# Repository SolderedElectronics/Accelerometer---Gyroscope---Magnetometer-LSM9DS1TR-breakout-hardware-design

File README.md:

# Accelerometer & Gyroscope & Magnetometer LSM9DS1TR 9-DOF breakout Hardware Design

## About the Product

|  |
| :----------------------------------------------------------: |
| [Buy Accelerometer & Gyroscope & Magnetometer LSM9DS1TR 9-DOF breakout](https://www.solde.red/333069) |

Discover the magic of motion tracking with our all-in-one Accelerometer, Gyroscope & Magnetometer LSM9DS1TR Breakout! This mini but mighty module bundles together a 3D accelerometer, a 3D gyroscope, and a 3D magnetometer. It lets you monitor not only linear and rotational movements but also the magnetic field surrounding your projects. Despite its pocket-size, it offers high-accuracy measurements — ±16 g for the accelerometer, ±2000 dps for the gyroscope, and ±16 Gauss for the magnetometer.

It has an embedded temperature sensor, FIFO buffer for data management, and interrupt features to signal your microcontroller when data is ready or when a certain event occurs. Plus, with I2C interface, it can easily connect with a variety of microcontrollers.

Our LSM9DS1TR breakout merges high-end capabilities with a user-friendly approach. It operates within a supply voltage range of 2.4V to 3.6V, making it compatible with both 3.3V and 5V systems. Its low-power and power-down modes optimize performance without draining too much energy.

This breakout board comes with 2 easyC connectors which will simplify connection with microcontrollers. By using the easyC module connection system, forget about incorrectly connected or, in the worst case, damaged modules.

---

## Repository Contents

This repository contains all design files for Accelerometer & Gyroscope & Magnetometer LSM9DS1TR 9-DOF breakout, organized as follows:

- **`CAD` folder**: Contains KiCAD design files, including:
  - Schematics
  - PCB layout
  - Panel PCB layout
  - Source 3D files in Fusion360, if any
  - All files are sorted by version with a detailed change log.
- **`OUTPUTS` folder**: Includes all production-ready files, such as:
  - Bill of Materials (BOM) and interactive BOM (iBOM)
  - PDF versions of schematics
  - 3D `.step` file of the board
  - 3D-printable models
  - Gerber files for PCB manufacturing
  - Image of the pinout of the board
  - Product image
  - Compliance, legal and generic sales documents

Refer to the `Change Log` in the CAD folder for details about updates between versions.

---

## Learn More About the Product

Beyond the repository, explore the following resources:

### Soldered Verify

The **Soldered Verify** system ensures every board you purchase from Soldered is fully functional. It also provides access to exclusive test data for your product. To get started, find the unique Soldered Verify ID on your product's packaging and enter the ID on the [Soldered Verify page](https://soldered.com/verify/) to access test results and additional product details.

### Soldered Community

Soldered Community is your go-to place for technical support. Our engineers track and answer all questions posted there, and it’s a great space for the maker community. Get answers to your questions and solutions for your challenges at [Soldered Community](https://soldered.com/community).

### solde.red

solde.red is an ultimate URL shortener and information hub. Access it by typing solde.red/ followed by your product SKU, e.g., [solde.red/333000](https://solde.red/333000), to find getting-started guides, datasheets, open-source hardware and software files, certifications, images, pinouts, and more. Read more about the shortener [here](https://solde.red/info/).

---

## Contributing

Contributions are welcome! Here’s how you can get involved:

- Submit pull requests to enhance the design or fix issues.
- Report bugs or problems by opening an issue.

We encourage community collaboration to make this product even better.

---

## About Soldered

[Soldered for Makers](https://soldered.com) specializes in designing and manufacturing electronic products tailored for enthusiasts, ranging from hobbyists to professionals. Our portfolio includes electronic boards, sensors, and actuators that are widely utilized in fields such as microelectronics, mechatronics, robotics, programming, and IoT. Every product we offer is designed in-house and built upon open-source hardware and software platforms. Proudly certified and manufactured within the European Union, our catalog likely includes the product you need for your project.

We complement these products with comprehensive tutorials and manuals, product descriptions, schematics, programming codes, and project examples. Our round-the-clock [customer and technical support](https://soldered.com/community) is available for all our products, irrespective of the sales channel. Soldered’s success and services reflect our maker community’s unwavering [trust](https://www.trustpilot.com/review/soldered.com), for which we are deeply grateful. Join our community and create using Soldered products.

---

## License

All Soldered open-source hardware (OSH) is under The TAPR Open Hardware License. Read more in the LICENSE file located in this repository.

**Disclaimer:**

No warranty - all designs in this repository are distributed in the hope that they will be useful, but without any warranty. They are provided "AS IS", therefore without warranty of any kind, either expressed or implied. The entire quality and performance of what you do with the contents of this repository are your responsibility. In no event Soldered Electronics will be liable for your damages, or losses, including any general, special, incidental, or consequential damage arising out of the use or inability to use the contents of this repository. 

---

## Have fun!

Thank you for your support from your fellow makers at Soldered Electronics.

Happy Making!

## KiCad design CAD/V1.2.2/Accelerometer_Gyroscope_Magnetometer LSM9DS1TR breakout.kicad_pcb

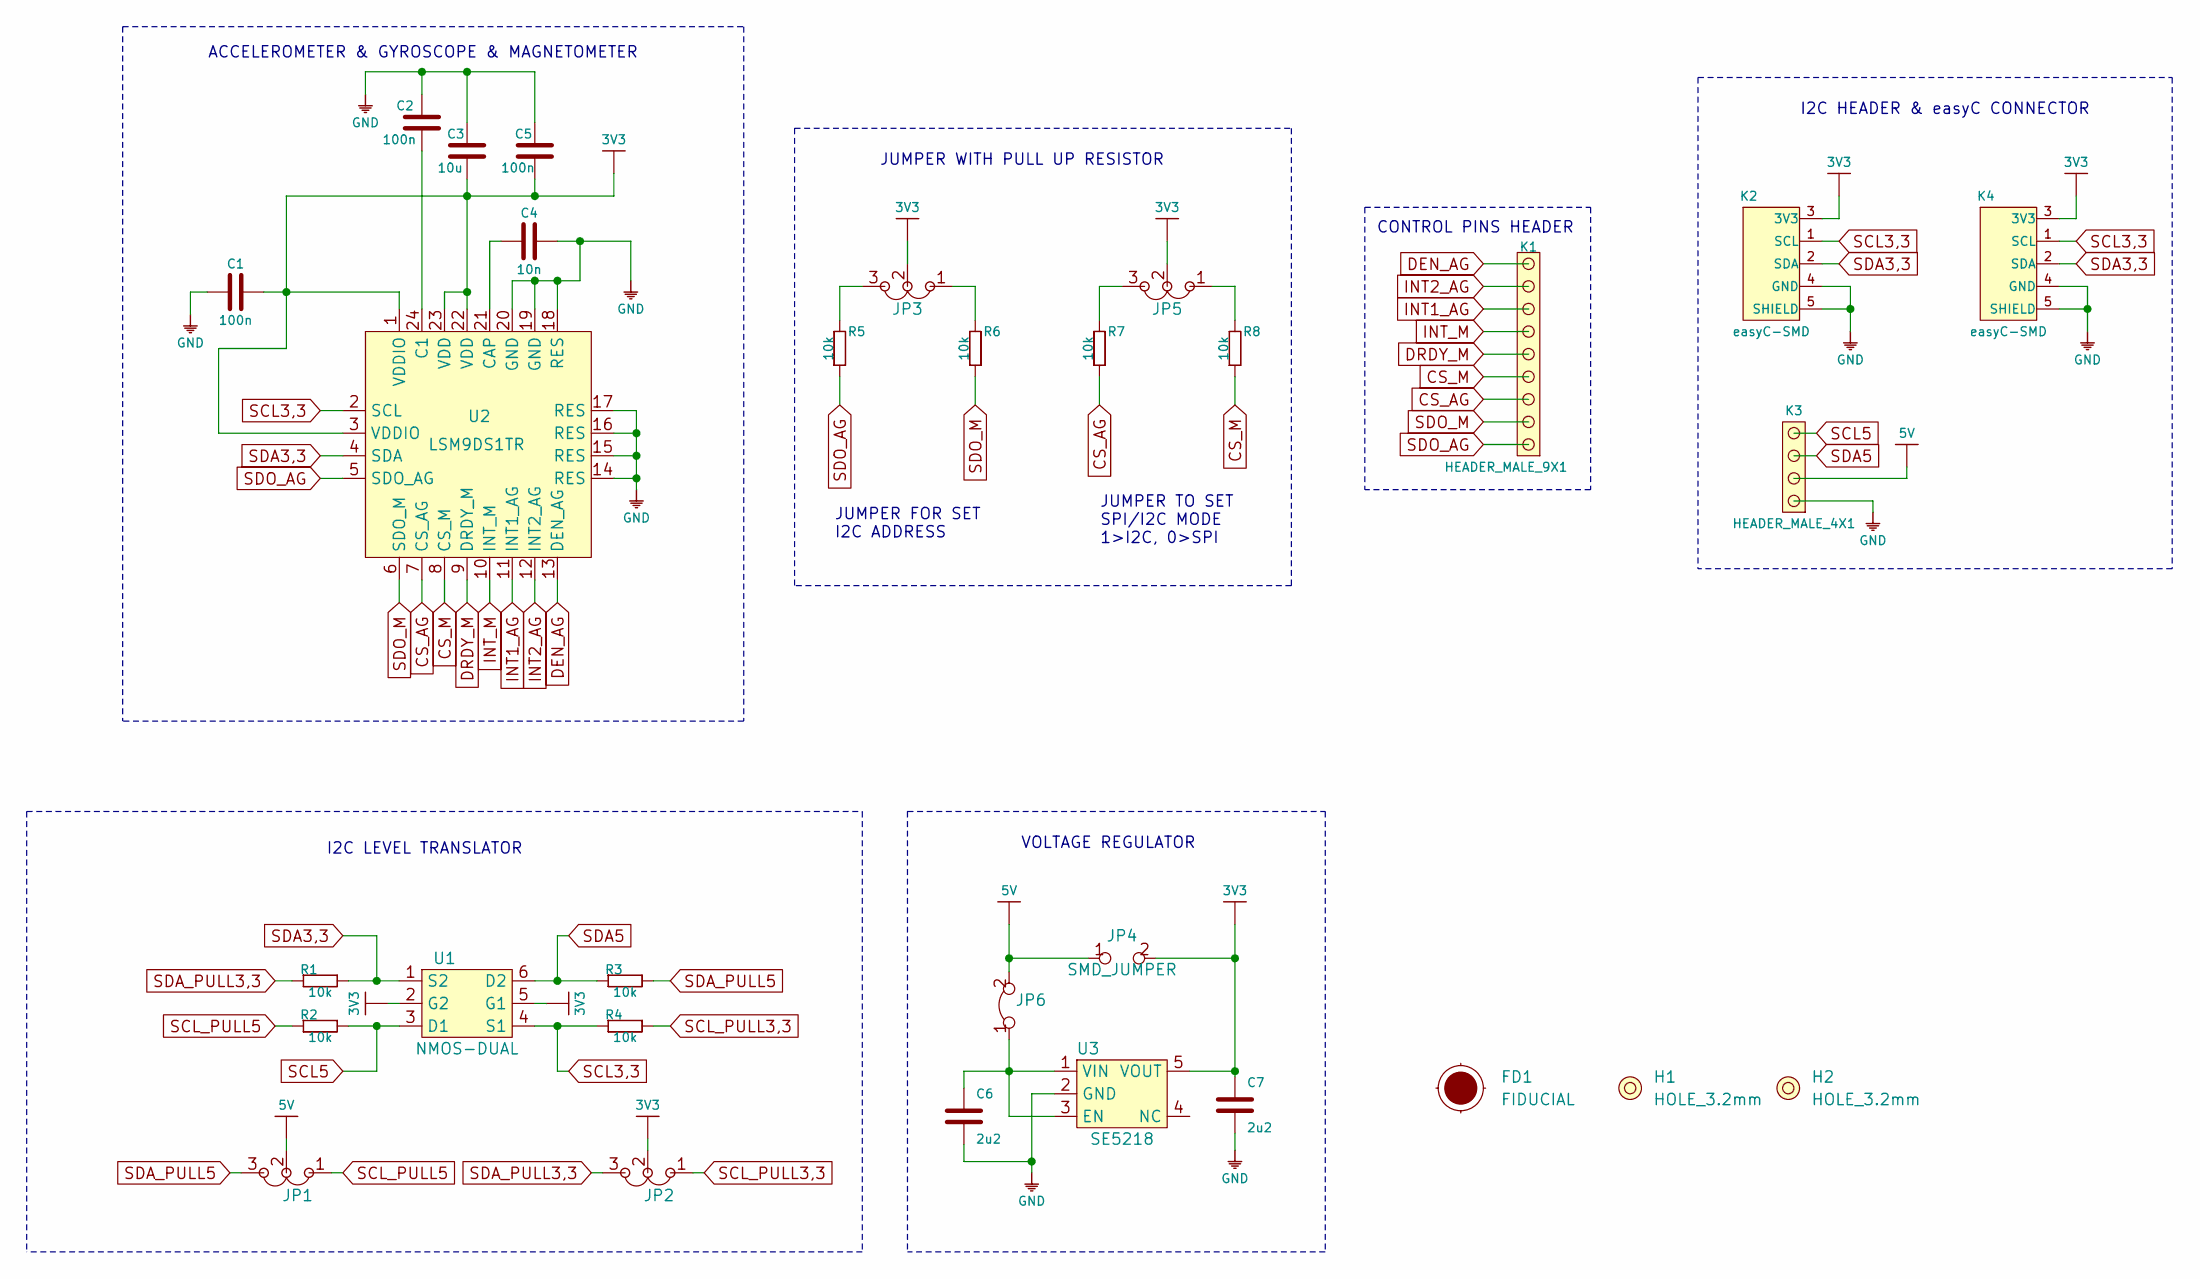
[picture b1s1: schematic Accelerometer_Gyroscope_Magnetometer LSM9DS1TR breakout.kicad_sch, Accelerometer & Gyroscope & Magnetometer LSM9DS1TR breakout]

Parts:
C1, C2, C5: 100n; 0603C
C3: 10u; 1206C
C4: 10n; 0603C
C6, C7: 2u2; 0603C
FD1: FIDUCIAL; FIDUCIAL_23
H1, H2: HOLE_3.2mm
JP1, JP2, JP3, JP5: SMD_JUMPER_3_PAD_TRACE
JP4: SMD_JUMPER
JP6: SMD-JUMPER-CONNECTED_TRACE_SLODERMASK
K1: HEADER_MALE_9X1
K2, K4: easyC-SMD; easyC-connector
K3: HEADER_MALE_4X1
R1, R2, R3, R4, R5, R6, R7, R8: 10k; 0603R
U1: NMOS-DUAL; SOT-363
U2: LSM9DS1TR
U3: SE5218; SOT-23-5

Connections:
3V3: C1.2, C3.1, C5.2, C7.2, JP2.2, JP3.2, JP4.2, JP5.2, K2.3 (3V3), K4.3 (3V3), U1.2 (G2), U1.5 (G1), U2.1 (VDDIO), U2.3 (VDDIO), U2.22 (VDD), U2.23 (VDD), U3.5 (VOUT)
5V: JP1.2, JP4.1, JP6.2, K3.2
CS_AG: K1.3, R7.1, U2.7 (CS_AG)
CS_M: K1.4, R8.1, U2.8 (CS_M)
DEN_AG: K1.9, U2.13 (DEN_AG)
DRDY_M: K1.5, U2.9 (DRDY_M)
GND: C1.1, C2.2, C3.2, C4.2, C5.1, C6.1, C7.1, K2.4 (GND), K2.5 (SHIELD), K3.1, K4.4 (GND), K4.5 (SHIELD), U2.14 (RES), U2.15 (RES), U2.16 (RES), U2.17 (RES), U2.18 (RES), U2.19 (GND), U2.20 (GND), U3.2 (GND)
INT1_AG: K1.7, U2.11 (INT1_AG)
INT2_AG: K1.8, U2.12 (INT2_AG)
INT_M: K1.6, U2.10 (INT_M)
unnamed: C2.1, U2.24 (C1)
unnamed: C4.1, U2.21 (CAP)
unnamed: C6.2, JP6.1, U3.1 (VIN), U3.3 (EN)
unnamed: JP3.1, R6.2
unnamed: JP3.3, R5.2
unnamed: JP5.1, R8.2
unnamed: JP5.3, R7.2
SCL3,3: K2.1 (SCL), K4.1 (SCL), R4.1, U1.4 (S1), U2.2 (SCL)
SCL5: K3.4, R2.2, U1.3 (D1)
SCL_PULL3,3: JP2.1, R4.2
SCL_PULL5: JP1.1, R2.1
SDA3,3: K2.2 (SDA), K4.2 (SDA), R1.2, U1.1 (S2), U2.4 (SDA)
SDA5: K3.3, R3.1, U1.6 (D2)
SDA_PULL3,3: JP2.3, R1.1
SDA_PULL5: JP1.3, R3.2
SDO_AG: K1.1, R5.1, U2.5 (SDO_AG)
SDO_M: K1.2, R6.1, U2.6 (SDO_M)

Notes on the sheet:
CONTROL PINS HEADER
JUMPER WITH PULL UP RESISTOR
ACCELEROMETER & GYROSCOPE & MAGNETOMETER
VOLTAGE REGULATOR
JUMPER FOR SET I2C ADDRESS
JUMPER TO SET SPI/I2C MODE 1>I2C, 0>SPI
I2C HEADER & easyC CONNECTOR
I2C LEVEL TRANSLATOR

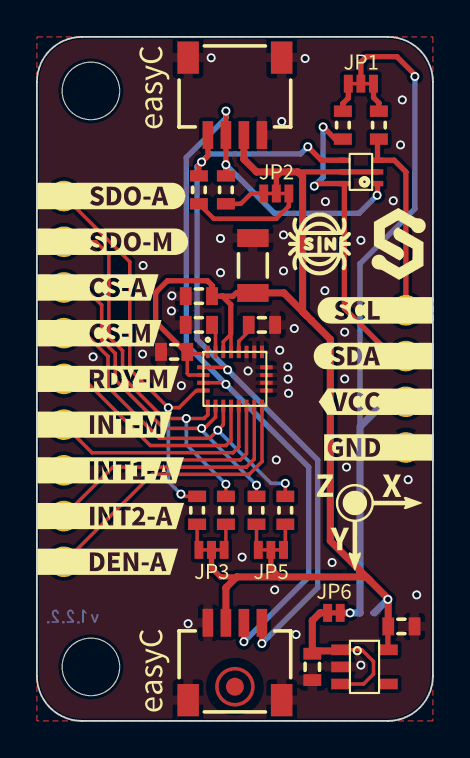
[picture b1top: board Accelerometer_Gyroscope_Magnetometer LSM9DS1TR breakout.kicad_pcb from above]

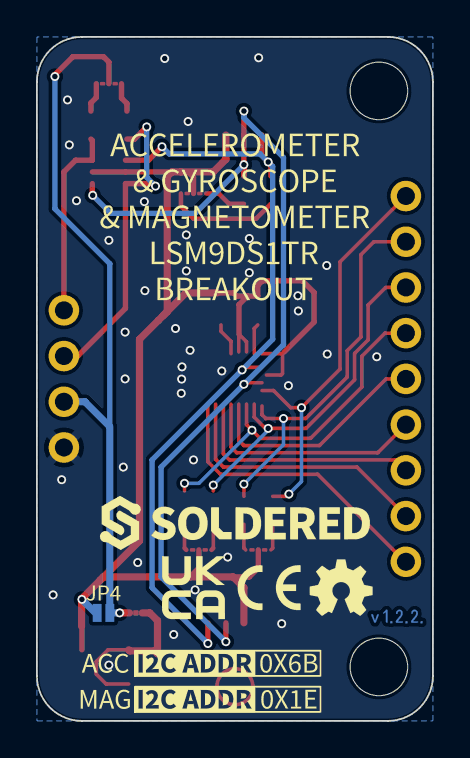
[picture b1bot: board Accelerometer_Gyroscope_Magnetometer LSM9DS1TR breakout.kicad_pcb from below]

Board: 2 copper layers, 22.0 x 38.0 mm, 59 parts (13 on the bottom side), 27 nets.

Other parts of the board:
kibuzzard-646B23F4: G***; kibuzzard-646B23F4
kibuzzard-6411B0B5: G***; kibuzzard-6411B0B5
kibuzzard-6411B0E0: G***; kibuzzard-6411B0E0
kibuzzard-6411B0F4: G***; kibuzzard-6411B0F4
kibuzzard-6411B1B6: G***; kibuzzard-6411B1B6
kibuzzard-6411B1E2: G***; kibuzzard-6411B1E2
kibuzzard-6411B1FF: G***; kibuzzard-6411B1FF
kibuzzard-6411B2B7: G***; kibuzzard-6411B2B7
kibuzzard-6411B2D2: G***; kibuzzard-6411B2D2
kibuzzard-6411B06B: G***; kibuzzard-6411B06B
kibuzzard-6411B07F: G***; kibuzzard-6411B07F
kibuzzard-6411B21F: G***; kibuzzard-6411B21F
kibuzzard-6411B22F: G***; kibuzzard-6411B22F
kibuzzard-6411B25F: G***; kibuzzard-6411B25F
kibuzzard-6411B32F: G***; kibuzzard-6411B32F
kibuzzard-6411B33C: G***; kibuzzard-6411B33C
kibuzzard-6411B059: G***; kibuzzard-6411B059
kibuzzard-6411B061: G***; kibuzzard-6411B061
kibuzzard-6411B074: G***; kibuzzard-6411B074
kibuzzard-6411B103: G***; kibuzzard-6411B103
kibuzzard-6411B119: G***; kibuzzard-6411B119
kibuzzard-6411B182: G***; kibuzzard-6411B182
kibuzzard-6411B196: G***; kibuzzard-6411B196
kibuzzard-6411B241: G***; kibuzzard-6411B241
kibuzzard-6411B292: G***; kibuzzard-6411B292
kibuzzard-6411B295: G***; kibuzzard-6411B295
kibuzzard-6411B327: G***; kibuzzard-6411B327
kibuzzard-6411B347: G***; kibuzzard-6411B347

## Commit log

2022-08-06 Updating open source files.
